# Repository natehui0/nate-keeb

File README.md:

# nate-keeb

# Custom Mechanical Keyboard

A custom mechanical keyboard designed and built from scratch using KiCad and Onshape. This project started as a way for me to learn more about PCB design, electronics, CAD, and mechanical keyboards, while pursuing my interest in keyboards.

# Project Pictures

Keyboard Design

Schematic

PCB

3D Model

Case

Code

# Bill of Materials

| Item | Price | Link |
|---|---:|---|
| Outemu Dustproof Switch RGB 3-Pin Linear (90 CT) | $28.25 | [AliExpress](https://www.aliexpress.us/item/3256805031592999.html) |
| White DUROCK Plate Mount Stabilizers V3 | $6.85 | [AliExpress](https://www.aliexpress.us/item/3256806342416791.html) |
| Fast Switching Schottky Diode (100 CT) | $4.71 | [AliExpress](https://www.aliexpress.us/item/3256812066033417.html) |
| Blank PBT Keycaps Set (DIY) | $16.35 | [AliExpress](https://www.aliexpress.us/item/3256808499333851.html) |
| Raspberry Pi Pico RP2040 Board | $3.65 | [AliExpress](https://www.aliexpress.us/item/3256805901509044.html) |
| PCB | $51.99 | [NextPCB](https://www.nextpcb.com/) |
| Additional AliExpress Fees | $4.50 | N/A |
| **Total** | **$116.30** | |

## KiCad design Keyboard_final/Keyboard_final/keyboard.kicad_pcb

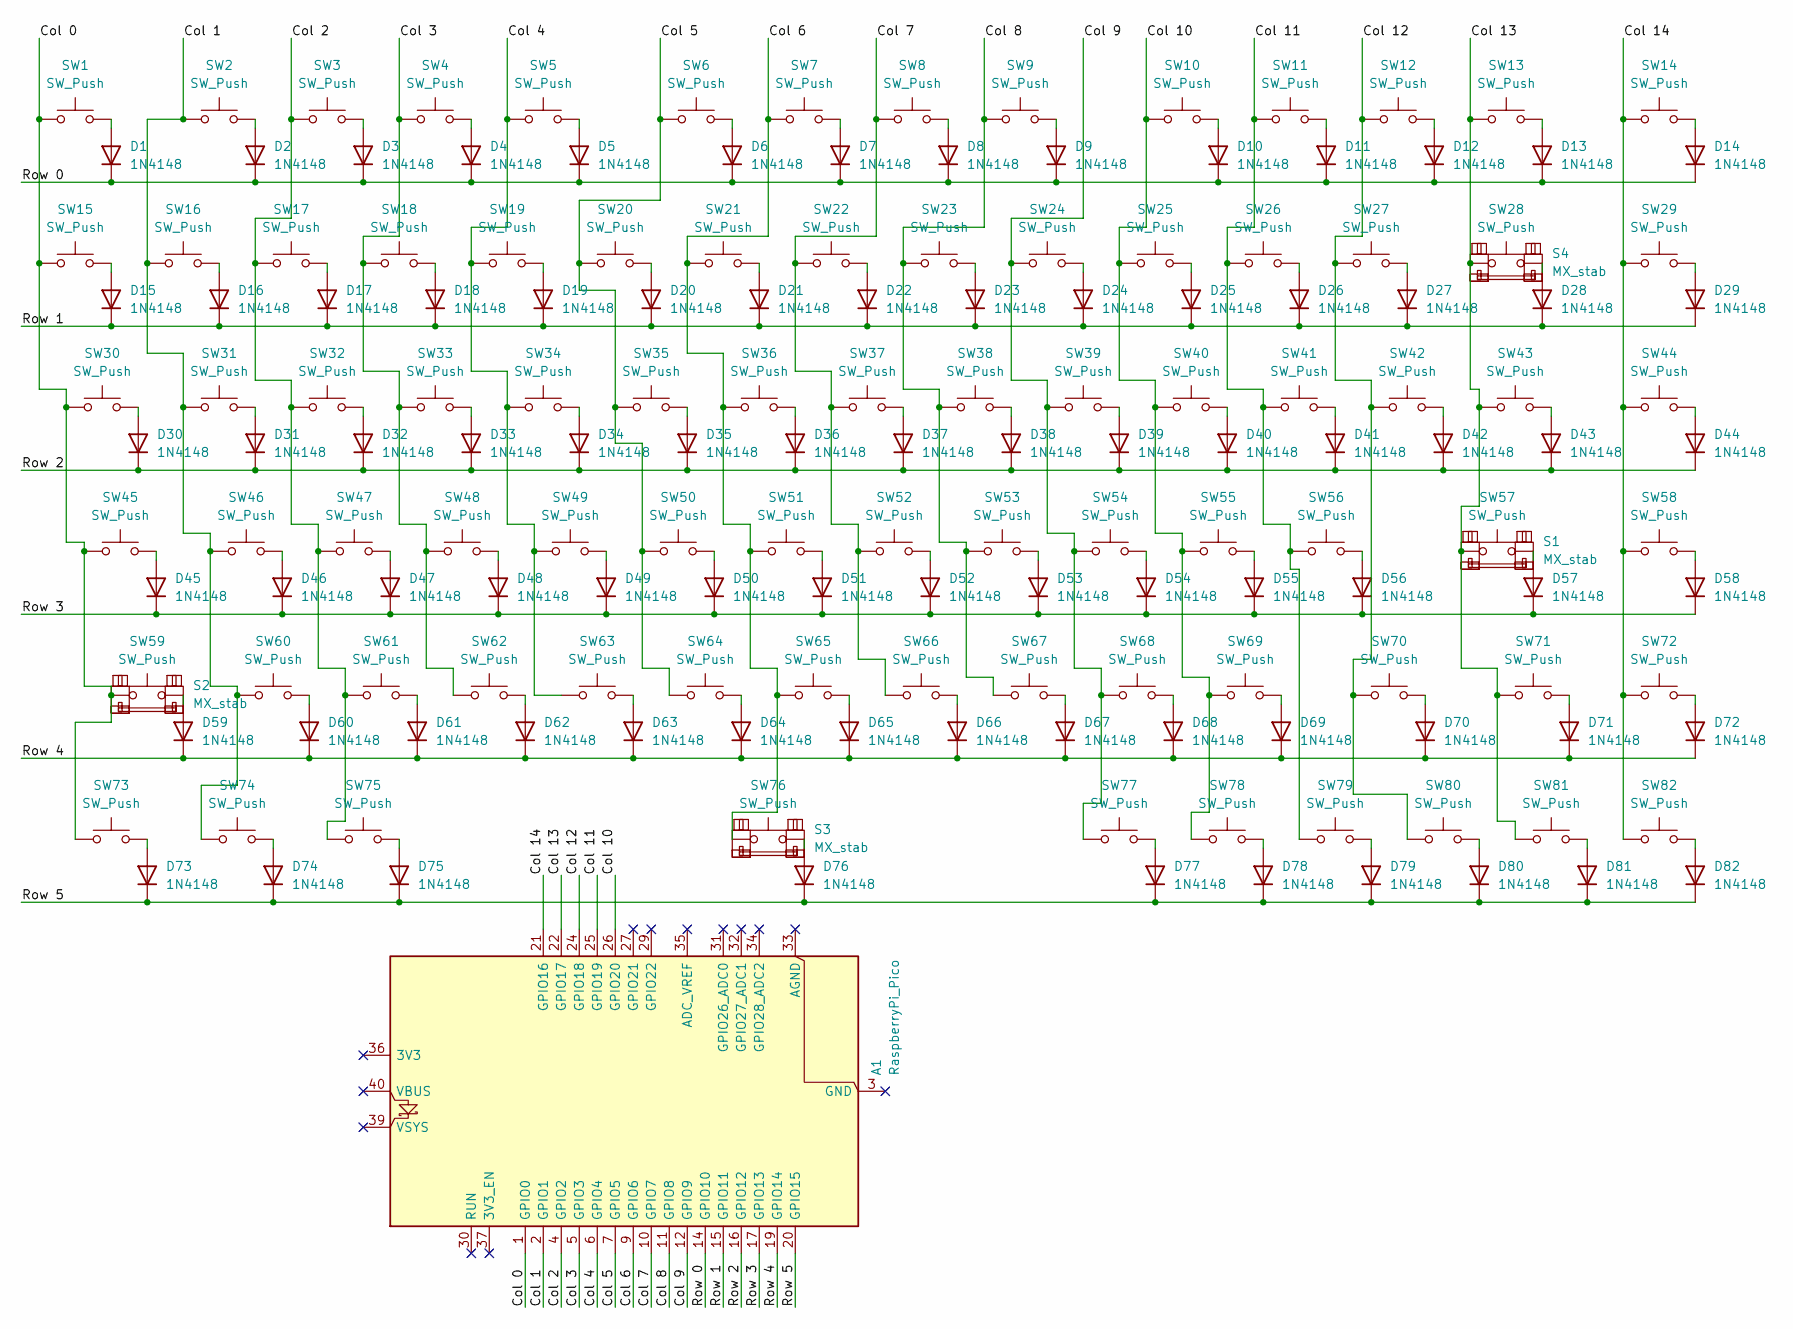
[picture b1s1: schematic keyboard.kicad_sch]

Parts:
A1: RaspberryPi_Pico; RaspberryPi_Pico_Common_THT
D1, D2, D3, D4, D5, D6, D7, D8, D9, D10, D11, D12, D13, D14, D15, D16, D17, D18, D19, D20, D21, D22, D23, D24, D25, D26, D27, D28, D29, D30, D31, D32, D33, D34, D35, D36, D37, D38, D39, D40, D41, D42, D43, D44, D45, D46, D47, D48, D49, D50, D51, D52, D53, D54, D55, D56, D57, D58, D59, D60, D61, D62, D63, D64, D65, D66, D67, D68, D69, D70, D71, D72, D73, D74, D75, D76, D77, D78, D79, D80, D81, D82: 1N4148; D_DO-35_SOD27_P7.62mm_Horizontal
S1, S2, S4: MX_stab; STAB_MX_P_2u
S3: MX_stab; STAB_MX_P_6.25u
SW1, SW2, SW3, SW4, SW5, SW6, SW7, SW8, SW9, SW10, SW11, SW12, SW13, SW14, SW15, SW16, SW17, SW18, SW19, SW20, SW21, SW22, SW23, SW24, SW25, SW26, SW27, SW28, SW29, SW30, SW31, SW32, SW33, SW34, SW35, SW36, SW37, SW38, SW39, SW40, SW41, SW42, SW43, SW44, SW45, SW46, SW47, SW48, SW49, SW50, SW51, SW52, SW53, SW54, SW55, SW56, SW57, SW58, SW59, SW60, SW61, SW62, SW63, SW64, SW65, SW66, SW67, SW68, SW69, SW70, SW71, SW72, SW73, SW74, SW75, SW76, SW77, SW78, SW79, SW80, SW81, SW82: SW_Push; SW_MX_1u

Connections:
/Col 0: A1.1 (GPIO0), SW1.1, SW15.1, SW30.1, SW45.1, SW59.1, SW73.1
/Col 1: A1.2 (GPIO1), SW2.1, SW16.1, SW31.1, SW46.1, SW60.1, SW74.1
/Col 2: A1.4 (GPIO2), SW3.1, SW17.1, SW32.1, SW47.1, SW61.1, SW75.1
/Col 3: A1.5 (GPIO3), SW4.1, SW18.1, SW33.1, SW48.1, SW62.1
/Col 4: A1.6 (GPIO4), SW5.1, SW19.1, SW34.1, SW49.1, SW63.1
/Col 5: A1.7 (GPIO5), SW6.1, SW20.1, SW35.1, SW50.1, SW64.1
/Col 6: A1.9 (GPIO6), SW7.1, SW21.1, SW36.1, SW51.1, SW65.1, SW76.1
/Col 7: A1.10 (GPIO7), SW8.1, SW22.1, SW37.1, SW52.1, SW66.1
/Col 8: A1.11 (GPIO8), SW9.1, SW23.1, SW38.1, SW53.1, SW67.1
/Col 9: A1.12 (GPIO9), SW24.1, SW39.1, SW54.1, SW68.1, SW77.1
/Col 10: A1.26 (GPIO20), SW10.1, SW25.1, SW40.1, SW55.1, SW69.1, SW78.1
/Col 11: A1.25 (GPIO19), SW11.1, SW26.1, SW41.1, SW56.1, SW79.1
/Col 12: A1.24 (GPIO18), SW12.1, SW27.1, SW42.1, SW70.1, SW80.1
/Col 13: A1.22 (GPIO17), SW13.1, SW28.1, SW43.1, SW57.1, SW71.1, SW81.1
/Col 14: A1.21 (GPIO16), SW14.1, SW29.1, SW44.1, SW58.1, SW72.1, SW82.1
/Row 0: A1.14 (GPIO10), D1.1 (K), D2.1 (K), D3.1 (K), D4.1 (K), D5.1 (K), D6.1 (K), D7.1 (K), D8.1 (K), D9.1 (K), D10.1 (K), D11.1 (K), D12.1 (K), D13.1 (K), D14.1 (K)
/Row 1: A1.15 (GPIO11), D15.1 (K), D16.1 (K), D17.1 (K), D18.1 (K), D19.1 (K), D20.1 (K), D21.1 (K), D22.1 (K), D23.1 (K), D24.1 (K), D25.1 (K), D26.1 (K), D27.1 (K), D28.1 (K), D29.1 (K)
/Row 2: A1.16 (GPIO12), D30.1 (K), D31.1 (K), D32.1 (K), D33.1 (K), D34.1 (K), D35.1 (K), D36.1 (K), D37.1 (K), D38.1 (K), D39.1 (K), D40.1 (K), D41.1 (K), D42.1 (K), D43.1 (K), D44.1 (K)
/Row 3: A1.17 (GPIO13), D45.1 (K), D46.1 (K), D47.1 (K), D48.1 (K), D49.1 (K), D50.1 (K), D51.1 (K), D52.1 (K), D53.1 (K), D54.1 (K), D55.1 (K), D56.1 (K), D57.1 (K), D58.1 (K)
/Row 4: A1.19 (GPIO14), D59.1 (K), D60.1 (K), D61.1 (K), D62.1 (K), D63.1 (K), D64.1 (K), D65.1 (K), D66.1 (K), D67.1 (K), D68.1 (K), D69.1 (K), D70.1 (K), D71.1 (K), D72.1 (K)
/Row 5: A1.20 (GPIO15), D73.1 (K), D74.1 (K), D75.1 (K), D76.1 (K), D77.1 (K), D78.1 (K), D79.1 (K), D80.1 (K), D81.1 (K), D82.1 (K)
unnamed: D1.2 (A), SW1.2
unnamed: D2.2 (A), SW2.2
unnamed: D3.2 (A), SW3.2
unnamed: D4.2 (A), SW4.2
unnamed: D5.2 (A), SW5.2
unnamed: D6.2 (A), SW6.2
unnamed: D7.2 (A), SW7.2
unnamed: D8.2 (A), SW8.2
unnamed: D9.2 (A), SW9.2
unnamed: D10.2 (A), SW10.2
unnamed: D11.2 (A), SW11.2
unnamed: D12.2 (A), SW12.2
unnamed: D13.2 (A), SW13.2
unnamed: D14.2 (A), SW14.2
unnamed: D15.2 (A), SW15.2
unnamed: D16.2 (A), SW16.2
unnamed: D17.2 (A), SW17.2
unnamed: D18.2 (A), SW18.2
unnamed: D19.2 (A), SW19.2
unnamed: D20.2 (A), SW20.2
unnamed: D21.2 (A), SW21.2
unnamed: D22.2 (A), SW22.2
unnamed: D23.2 (A), SW23.2
unnamed: D24.2 (A), SW24.2
unnamed: D25.2 (A), SW25.2
unnamed: D26.2 (A), SW26.2
unnamed: D27.2 (A), SW27.2
unnamed: D28.2 (A), SW28.2
unnamed: D29.2 (A), SW29.2
unnamed: D30.2 (A), SW30.2
unnamed: D31.2 (A), SW31.2
unnamed: D32.2 (A), SW32.2
unnamed: D33.2 (A), SW33.2
unnamed: D34.2 (A), SW34.2
unnamed: D35.2 (A), SW35.2
unnamed: D36.2 (A), SW36.2
unnamed: D37.2 (A), SW37.2
unnamed: D38.2 (A), SW38.2
unnamed: D39.2 (A), SW39.2
unnamed: D40.2 (A), SW40.2
unnamed: D41.2 (A), SW41.2
unnamed: D42.2 (A), SW42.2
unnamed: D43.2 (A), SW43.2
unnamed: D44.2 (A), SW44.2
unnamed: D45.2 (A), SW45.2
unnamed: D46.2 (A), SW46.2
unnamed: D47.2 (A), SW47.2
unnamed: D48.2 (A), SW48.2
unnamed: D49.2 (A), SW49.2
unnamed: D50.2 (A), SW50.2
unnamed: D51.2 (A), SW51.2
unnamed: D52.2 (A), SW52.2
unnamed: D53.2 (A), SW53.2
unnamed: D54.2 (A), SW54.2
unnamed: D55.2 (A), SW55.2
unnamed: D56.2 (A), SW56.2
unnamed: D57.2 (A), SW57.2
unnamed: D58.2 (A), SW58.2
unnamed: D59.2 (A), SW59.2
unnamed: D60.2 (A), SW60.2
unnamed: D61.2 (A), SW61.2
unnamed: D62.2 (A), SW62.2
unnamed: D63.2 (A), SW63.2
unnamed: D64.2 (A), SW64.2
unnamed: D65.2 (A), SW65.2
unnamed: D66.2 (A), SW66.2
unnamed: D67.2 (A), SW67.2
unnamed: D68.2 (A), SW68.2
unnamed: D69.2 (A), SW69.2
unnamed: D70.2 (A), SW70.2
unnamed: D71.2 (A), SW71.2
unnamed: D72.2 (A), SW72.2
unnamed: D73.2 (A), SW73.2
unnamed: D74.2 (A), SW74.2
unnamed: D75.2 (A), SW75.2
unnamed: D76.2 (A), SW76.2
unnamed: D77.2 (A), SW77.2
unnamed: D78.2 (A), SW78.2
unnamed: D79.2 (A), SW79.2
unnamed: D80.2 (A), SW80.2
unnamed: D81.2 (A), SW81.2
unnamed: D82.2 (A), SW82.2

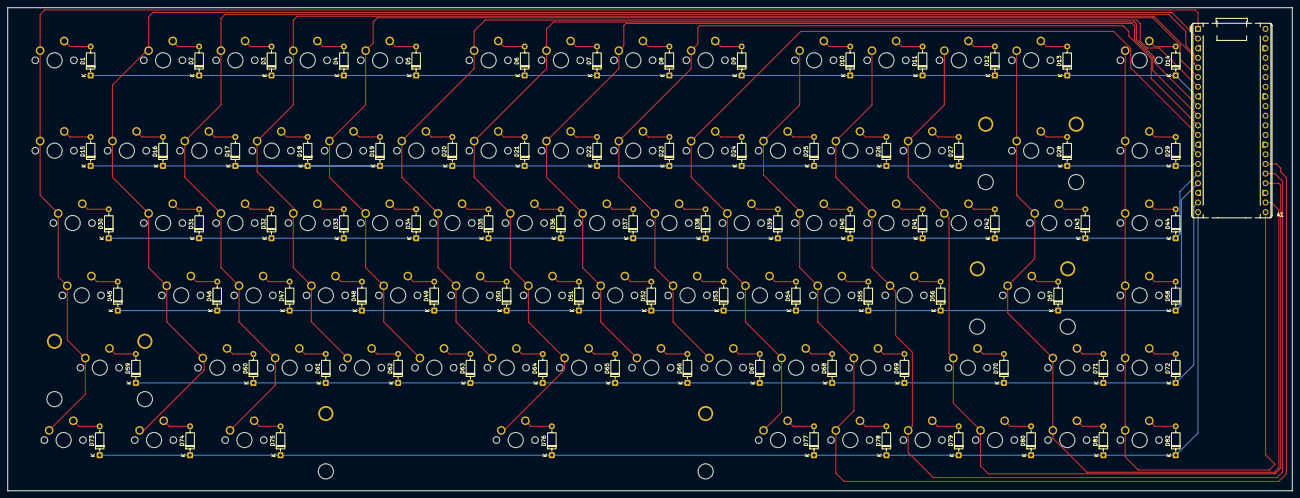
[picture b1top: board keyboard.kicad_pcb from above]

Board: 2 copper layers, 338.3 x 127.2 mm, 169 parts (0 on the bottom side), 103 nets.
